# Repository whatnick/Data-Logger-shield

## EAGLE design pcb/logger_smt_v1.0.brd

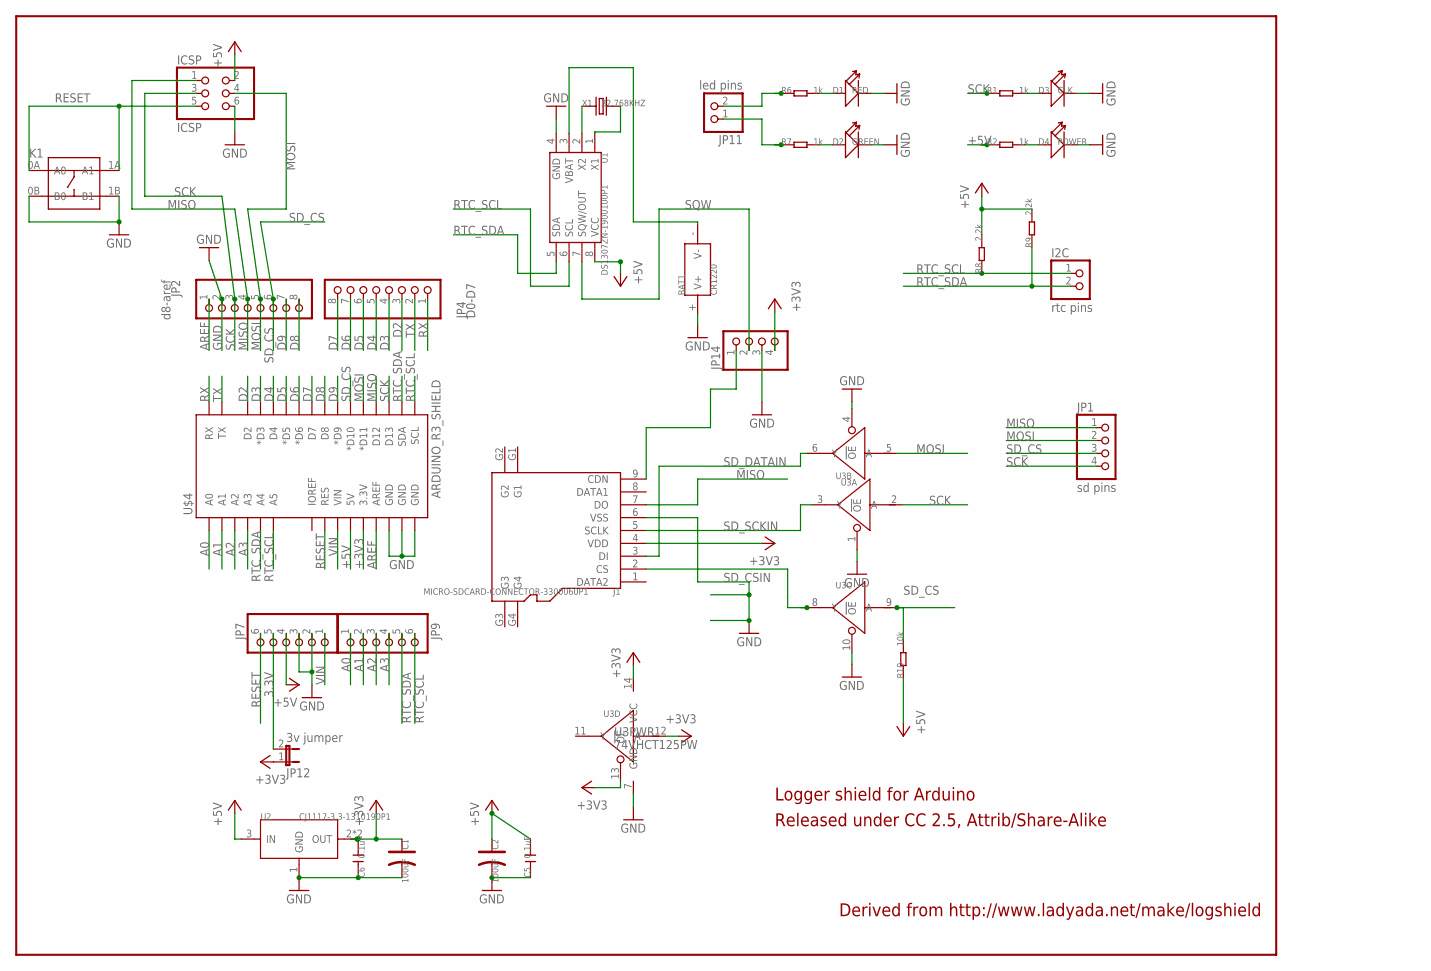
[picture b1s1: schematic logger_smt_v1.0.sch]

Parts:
BAT1: CR1220; PLASTIC-CR1220-L15.06XW13.0XH4.1MM
C1, C2: 100uF; ELECTRO-SMD-B-4.8MM
C5, C6: 0.1uF; C0603
D1: RED; LED-0603
D2: GREEN; LED-0603
D3: CLK; LED-0603
D4: POWER; LED-0603
I2C: rtc pins; 1X02
ICSP: ICSP; 2X03
J1: MICRO-SDCARD-CONNECTOR-3300060P1; 9P-SMD-W-RING
JP1: sd pins; 1X04
JP2: d8-aref; 1X08-BIG
JP4: D0-D7; 1X08-BIG
JP7, JP9: PINHD-1X6B; 1X06-BIG
JP11: led pins; 1X02
JP12: 3v jumper; JP1
JP14: PINHD-1X4; 1X04
K1: BUTTON-4P-6X6-SMD; 4P-SMD-6.2X6.2X4H
R1, R2, R6, R7: 1k; R0603
R8, R9: 2.2k; R0603
R10: 10k; R0603
U1: DS1307ZN-1900100P1; SOIC8
U2: CJ1117-3.3-1310190P1; SOT223
U3: 74VHCT125PW; TSSOP14
U$4: ARDUINO_R3_SHIELD; UNO_R3_SHIELD
X1: 32.768KHZ; 2P-SMD-3.2X1.5

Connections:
3.3V: JP7.5, JP12.2
+3V3: C1.+, C6.2, J1.4 (VDD), JP12.1, JP14.4, U2.2 (OUT), U2.TER (OUT), U3.12 (A), U3.13 (!OE), U3.14 (VCC), U$4.3.3V
+5V: C2.+, C5.2, ICSP.2, JP7.4, R2.1, R8.2, R9.2, R10.1, U1.8 (VCC), U2.3 (IN), U$4.5V
A0: JP9.1, U$4.A0
A1: JP9.2, U$4.A1
A2: JP9.3, U$4.A2
A3: JP9.4, U$4.A3
AREF: JP2.1, U$4.AREF
D2: JP4.3, U$4.D2
D3: JP4.4, U$4.D3 (*D3)
D4: JP4.5, U$4.D4
D5: JP4.6, U$4.D5 (*D5)
D6: JP4.7, U$4.D6 (*D6)
D7: JP4.8, U$4.D7
D8: JP2.8, U$4.D8
D9: JP2.7, U$4.D9 (*D9)
GND: BAT1.+ (V+), C1.-, C2.-, C5.1, C6.1, D1.-, D2.-, D3.-, D4.-, ICSP.6, J1.6 (VSS), JP2.2, JP7.2, JP7.3, JP14.3, K1.0B (B0), K1.1B (B1), U1.4 (GND), U2.1 (GND), U3.1 (!OE), U3.4 (!OE), U3.7 (GND), U3.10 (!OE), U$4.GND@0 (GND), U$4.GND@1 (GND), U$4.GND@2 (GND)
MISO: ICSP.1, J1.7 (DO), JP1.1, JP2.4, U$4.D12
MOSI: ICSP.4, JP1.2, JP2.5, U3.5 (A), U$4.D11 (*D11)
unnamed: BAT1.- (V-), U1.3 (VBAT)
unnamed: U1.2 (X2), X1.1
unnamed: U1.1 (X1), X1.2
unnamed: D1.+, R6.2
unnamed: JP11.2, R6.1
unnamed: D2.+, R7.2
unnamed: JP11.1, R7.1
unnamed: D3.+, R1.2
unnamed: D4.+, R2.2
RESET: ICSP.5, JP7.6, K1.0A (A0), K1.1A (A1), U$4.RES
RTC_SCL: I2C.1, JP9.6, R8.1, U1.6 (SCL), U$4.A5, U$4.SCL
RTC_SDA: I2C.2, JP9.5, R9.1, U1.5 (SDA), U$4.A4, U$4.SDA
RX: JP4.1, U$4.RX
SCK: ICSP.3, JP1.4, JP2.3, R1.1, U3.2 (A), U$4.D13
SD_CD: J1.9 (CDN), JP14.1
SD_CS: JP1.3, JP2.6, R10.2, U3.9 (A), U$4.D10 (*D10)
SD_CSIN: J1.2 (CS), U3.8 (Y)
SD_DATAIN: J1.3 (DI), U3.6 (Y)
SD_SCKIN: J1.5 (SCLK), U3.3 (Y)
SQW: JP14.2, U1.7 (SQW/OUT)
TX: JP4.2, U$4.TX
VIN: JP7.1, U$4.VIN

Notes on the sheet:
Derived from http://www.ladyada.net/make/logshield
Released under CC 2.5, Attrib/Share-Alike
Logger shield for Arduino

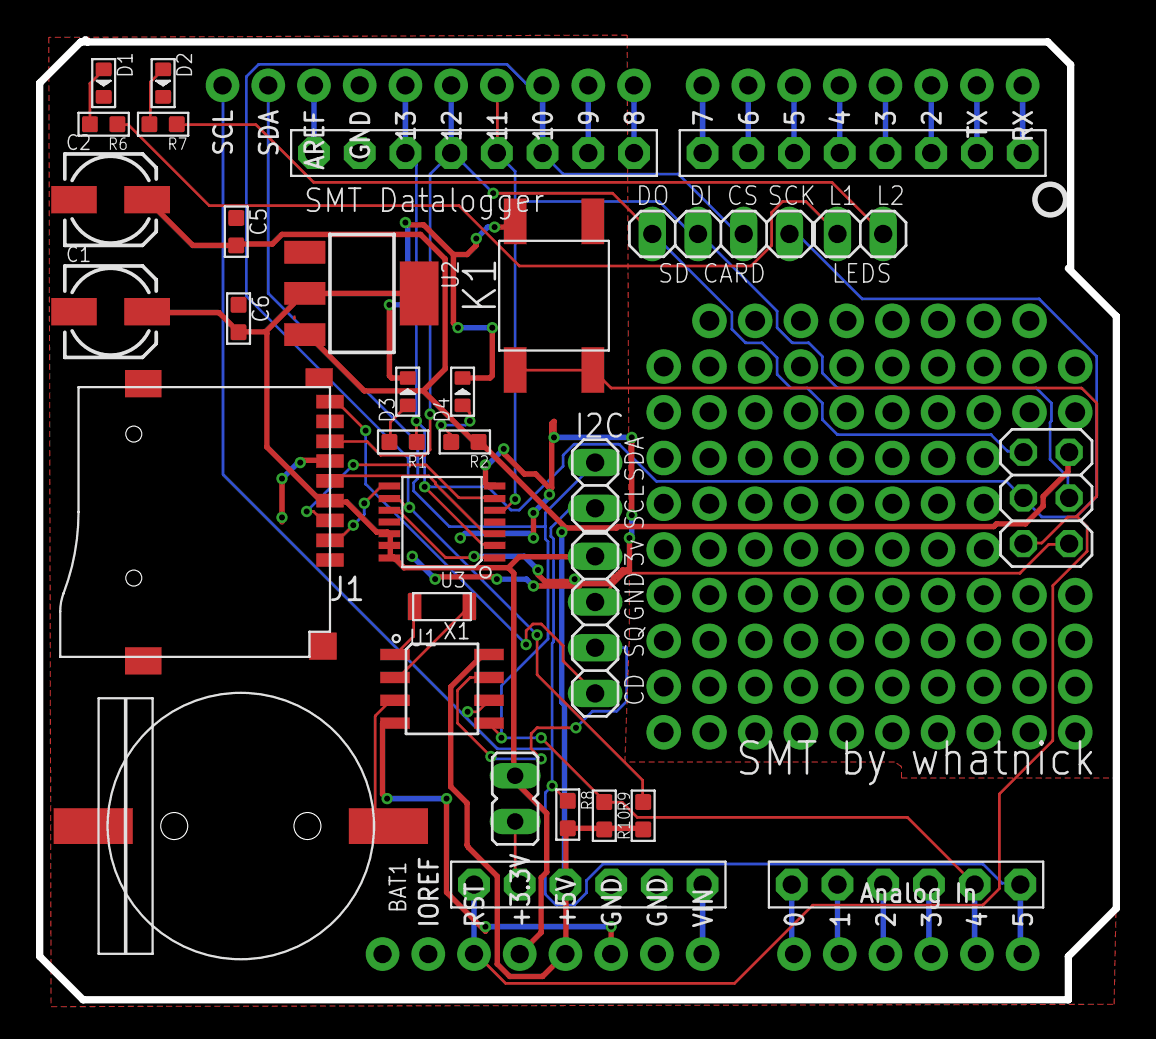
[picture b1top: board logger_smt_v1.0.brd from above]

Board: 2 copper layers, 59.8 x 53.3 mm, 33 parts (0 on the bottom side), 41 nets.

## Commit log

2014-10-23 Converted to OPL SMD components
2014-10-23 Mostly wired up
2014-10-23 Added extra LED's, finished wiring
2014-10-23 Changed and rerouted to match OPL availability
2014-10-24 Minor silk screen change
2014-10-24 Changed attribution and removed adafruit trademark

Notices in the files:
parts and their libraries:
SparkFun-Boards: Licensing: Creative Commons ShareAlike 4.0 International - https://creativecommons.org/licenses/by-sa/4.0
